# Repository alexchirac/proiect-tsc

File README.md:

## © Copyright Chirac Alexandru-Stefan 333CA

# Hardware Overview and Component Specifications

This document outlines the key hardware components used in the system, including their roles and detailed specifications.

---

## 📑 Table of Contents

- [Main Controller](#main-controller)
- [Display System](#display-system)
- [Power](#power)
- [Memory and Storage](#memory-and-storage)
- [Sensors](#sensors)
- [Connectivity](#connectivity)
- [Block diagram](#block-diagram)
- [Pin Assignments](#pin-assignments)
- [Bill of Materials](#bill-of-materials)

---

## Main Controller

### ESP32-C6-WROOM-1-N8
- **Function**: Core microcontroller that manages all system operations.

---

## Display System

### E-Paper Display
- **Drive Circuit**: Custom electronics for controlling the display.
- **Display Type Selector**: Configurable support for different e-paper types.

---

## Power

### LDO Voltage Regulator — XC6220A331MR-G
- **Function**: Supplies regulated 3.3V to the system.
- **Input Voltage**: Up to 6.0 V
- **Output Current**: Up to 700 mA

### Battery Charger — MCP73831
- **Function**: Manages Li-Po battery charging.
- **Charge Current**: Up to 500 mA (programmable)
- **Charge Voltage**: Fixed at 4.2 V
- **Input Voltage**: Typically 5 V (USB)
- **Features**: Thermal protection, automatic termination, LED status indicator

### Battery Fuel Gauge — MAX17048G+T10
- **Function**: Monitors battery state-of-charge and voltage.
- **Interface**: I2C
- **Voltage Accuracy**: ±7.5 mV
- **Current Consumption**: ~23 µA

### Supercapacitor — CPH3225A
- **Function**: Provides short-term backup power during power loss.

### Diode — MBR0530
- **Function**: Reverse voltage protection and efficient switching.
- **Max Current**: 0.5 A
- **Forward Voltage**: ~0.3–0.4 V

---

## Memory and Storage

### External NOR Flash — W25Q512JVEIQ
- **Function**: High-capacity external storage.
- **Capacity**: 512 Mbit (64 MB)
- **Interface**: SPI
- **Voltage**: 3.3 V
- **Usage**: Firmware, configuration data, graphical assets

### SD Card Slot
- **Function**: Expandable storage option for user or application data.

---

## Sensors

### Environmental Sensor — BME688
- **Function**: Measures environmental data.
- **Measurements**: Temperature, Humidity, Pressure, VOC gas
- **Interface**: I2C
- **Operating Voltage**: 1.7 V – 3.6 V

### RTC Module — DS3231SN
- **Function**: Maintains accurate timekeeping.
- **Accuracy**: ±2 ppm (~1 minute/year)
- **Interface**: I2C
- **Voltage**: 2.3 V – 5.5 V
- **Feature**: Integrated battery backup

---

## Connectivity

### USB-C Connector
- **Function**: Provides both power input and data communication.

### ESD Protection — USBLC6-2SC6Y
- **Function**: Protects USB lines from electrostatic discharge.

### Qwiic/Stemma QT Connector
- **Function**: Supports I2C-based expansion modules.

---

## Block Diagram

---

## Pin Assignments

| ESP32-C6 Pin | Function       | Connected To               | Description                           |
|--------------|----------------|----------------------------|---------------------------------------|
| 3            | RESET          | Reset Button               | System hardware reset                 |
| 4            | SS_SD          | SD Card (pin 2)            | SPI Slave Select for SD card          |
| 6            | SCK            | SD Card (pin 5)            | SPI Clock signal                      |
| 7            | MOSI           | SD Card (pin 3)            | SPI Master Out Slave In               |
| 8            | INT_RTC        | RTC Module (pin 3)         | Interrupt signal from RTC             |
| 9            | 32KHz          | RTC Module (pin 1)         | 32KHz clock signal from RTC           |
| 13           | USB_D-         | USB-C Connector (pin 3)    | USB Data Negative line                |
| 14           | USB_D+         | USB-C Connector (pin 1)    | USB Data Positive line                |
| 15           | IO/BOOT        | Boot Button                | Boot mode selector button             |
| 16           | RTC_RST        | RTC Module (pin 4)         | RTC reset control                     |
| 17           | I2C_PW         | BME688 Sensor (pins 6, 8, 2)| Power control for environmental sensor|
| 19           | SDA            | Multiple I²C devices       | I²C Serial Data line (shared)         |
| 20           | SCL            | Multiple I²C devices       | I²C Serial Clock line (shared)        |
| 23           | IO/CHANGE      | Change Button              | Display/Mode change button            |
| 27           | MISO           | SD Card (pin 7)            | SPI Master In Slave Out               |

---

## Bill of Materials

 | Device | Qty | PURCHASE-URL |
 |--------|-----|--------------|
 | ADAFRUIT_LEDCHIP-LED0603 | 1 | https://www.snapeda.com/parts/KP-1608SURCK/Kingbright/view-part/?ref=search&t=LED%200603 | 
 | EAGLE-LTSPICE_CC0402 | 1 | https://componentsearchengine.com/part-view/CC0402MRX5R5BB106/YAGEO | 
 | RCL_CPOL-EUCT3528 | 1 | https://a360.co/4iZy6AA | 
 | SJ | 1 | https://grabcad.com/library/solder-jumpers-1 | 
 | VARISTOR_3216 | 1 | https://www.mouser.co.uk/ProductDetail/EPCOS-TDK/B72520T0350K062?qs=dEfas%2FXlABIszF52uu7vrg%3D%3D | 
 | EAGLE-LTSPICE_CC0402 | 1 | https://componentsearchengine.com/part-view/CC0402MRX5R5BB106/YAGEO | 
 | ESP32_WROVER_EAGLE-LTSPICE_RR0402 | 1 | https://componentsearchengine.com/part-view/R0402%201%25%20100%20K%20(RC0402FR-07100KL)/YAGEO | 
 | EAGLE-LTSPICE_CC0402 | 1 | https://componentsearchengine.com/part-view/CC0402MRX5R5BB106/YAGEO | 
 | ESP32_WROVER_EAGLE-LTSPICE_RR0402 | 1 | https://componentsearchengine.com/part-view/R0402%201%25%20100%20K%20(RC0402FR-07100KL)/YAGEO | 
 | EAGLE-LTSPICE_CC0402 | 7 | https://componentsearchengine.com/part-view/CC0402MRX5R5BB106/YAGEO | 
 | ESP32_WROVER_EAGLE-LTSPICE_RR0402 | 16 | https://componentsearchengine.com/part-view/R0402%201%%20100%20K%20(RC0402FR-07100KL)/YAGEO | 
 | EAGLE-LTSPICE_CC0402 | 1 | https://componentsearchengine.com/part-view/CC0402MRX5R5BB106/YAGEO | 
 | 112A-TAAR-R03_ATTEND | 1 | https://store.comet.srl.ro/Catalogue/Product/43497/ | 
 | ESP32_WROVER_EAGLE-LTSPICE_RR0402 | 1 | https://componentsearchengine.com/part-view/R0402%201%25%20100%20K%20(RC0402FR-07100KL)/YAGEO | 
 | EAGLE-LTSPICE_CC0402 | 1 | https://componentsearchengine.com/part-view/CC0402MRX5R5BB106/YAGEO | 
 | EAGLE-LTSPICE_CC0402 | 8 | https://componentsearchengine.com/part-view/CC0402MRX5R5BB106/YAGEO | 
 | EAGLE-LTSPICE_CC0402 | 1 | https://componentsearchengine.com/part-view/CC0402MRX5R5BB106/YAGEO | 
 | ESP32_WROVER_EAGLE-LTSPICE_RR0402 | 1 | https://componentsearchengine.com/part-view/R0402%201%25%20100%20K%20(RC0402FR-07100KL)/YAGEO | 
 | ESP32_WROVER_EAGLE-LTSPICE_RR0402 | 1 | https://componentsearchengine.com/part-view/R0402%201%25%20100%20K%20(RC0402FR-07100KL)/YAGEO | 
 | ESP32_WROVER_SPARKFUN-DISCRETESEMI_MOSFET_PCH-DMG2305UX-7 | 2 | https://componentsearchengine.com/part-view/SI1308EDL-T1-GE3/Vishay | 
 | ESP32_WROVER_EAGLE-LTSPICE_RR0402 | 1 | https://componentsearchengine.com/part-view/R0402%201%25%20100%20K%20(RC0402FR-07100KL)/YAGEO | 
 | EAGLE-LTSPICE_CC0402 | 1 | https://componentsearchengine.com/part-view/CC0402MRX5R5BB106/YAGEO | 
 | EAGLE-LTSPICE_CC0402 | 3 | https://componentsearchengine.com/part-view/CC0402MRX5R5BB106/YAGEO | 
 | EAGLE-LTSPICE_CC0402 | 1 | https://componentsearchengine.com/part-view/CC0402MRX5R5BB106/YAGEO | 
 | ESP32_WROVER_EAGLE-LTSPICE_RR0402 | 2 | https://componentsearchengine.com/part-view/R0402%201%25%20100%20K%20(RC0402FR-07100KL)/YAGEO | 
 | 744043680IND_4828-WE-TPC_WRE | 1 | https://eu.mouser.com/ProductDetail/Wurth-Elektronik/744043680?qs=PGXP4M47uW6VkZq%252BkzjrHA%3D%3D | 
 | BD5229G-TR | 1 | https://componentsearchengine.com/part-view/BD5229G-TR/ROHM%20Semiconductor | 
 | BUTTON_CUSYOMV1PACKAGE | 3 | https://www.snapeda.com/parts/EVQP7L01P/Panasonic/view-part/?ref=search&t=evqp7l | 
 | CPH3225A | 1 | https://www.snapeda.com/api/url_track_click_mouser/?unipart_id=562593&manufacturer=Seiko%20Instruments&part_name=CPH3225A&search_term=None | 
 | DS3231SN# | 1 | https://www.snapeda.com/api/url_track_click_mouser/?unipart_id=99048&manufacturer=Analog%20Devices&part_name=DS3231SN#&search_term=None | 
 | ESP32-C6-WROOM-1-N8 | 1 | https://www.snapeda.com/parts/ESP32-C6-WROOM-1-N8/Espressif+Systems/view-part/?ref=eda | 
 | ESP32_WROVER_AVX---SD0805S020S1R0_AVX_ SD0805S020S1R0_0_0AVX_SD0805S020S1R0_0_0 | 2 | https://eu.mouser.com/ProductDetail/KYOCERA-AVX/SD0805S020S1R0?qs=jCA%252BPfw4LHbpkAoSnwrdjw%3D%3D | 
 | ESP32_WROVER_BME680_BME680 | 1 | https://www.snapeda.com/parts/BME680/Bosch/view-part/?welcome=home | 
 | ESP32_WROVER_SPARKFUN-IC-POWER_MCP73831 | 1 | https://www.digikey.ro/en/products/detail/microchip-technology/MCP73831T-2ACI-OT/964301 | 
 | FH34SRJ-24S-0.5SH_99_ | 1 | https://componentsearchengine.com/part-view/XC6220A331MR-G/Torex | 
 | MAX17048G+T10 | 1 | https://www.snapeda.com/api/url_track_click_mouser/?unipart_id=329239&manufacturer=Analog%20Devices&part_name=MAX17048G+T10&search_term=None | 
 | MBR0530 | 3 | https://www.snapeda.com/api/url_track_click_mouser/?unipart_id=179458&manufacturer=ON%20Semiconductor&part_name=MBR0530&search_term=None | 
 | PGB1010603MR | 6 | https://www.snapeda.com/api/url_track_click_mouser/?unipart_id=5659453&manufacturer=Littelfuse%20Inc.&part_name=PGB1010603MR&search_term=None | 
 | QWIIC_CONNECTORJS-1MM | 1 | https://www.digikey.ro/en/models/926710 | 
 | SAMACSYS_PARTS_USB4110-GF-A | 1 | https://componentsearchengine.com/part-view/USB4110-GF-A/GCT%20(GLOBAL%20CONNECTOR%20TECHNOLOGY) | 
 | SI1308EDL-T1-GE3 | 1 | https://componentsearchengine.com/part-view/SI1308EDL-T1-GE3/Vishay | 
 | TPTP20R | 17 | https://grabcad.com/library/test-points-printed-circuit-board-1 | 
 | USBLC6-2SC6Y | 1 | https://www.snapeda.com/parts/USBLC6-2SC6Y/STMicroelectronics/view-part/?ref=eda | 
 | W25Q512JVEIQ | 1 | https://www.snapeda.com/parts/W25Q512JVEIQ/Winbond+Electronics/view-part/?ref=eda |

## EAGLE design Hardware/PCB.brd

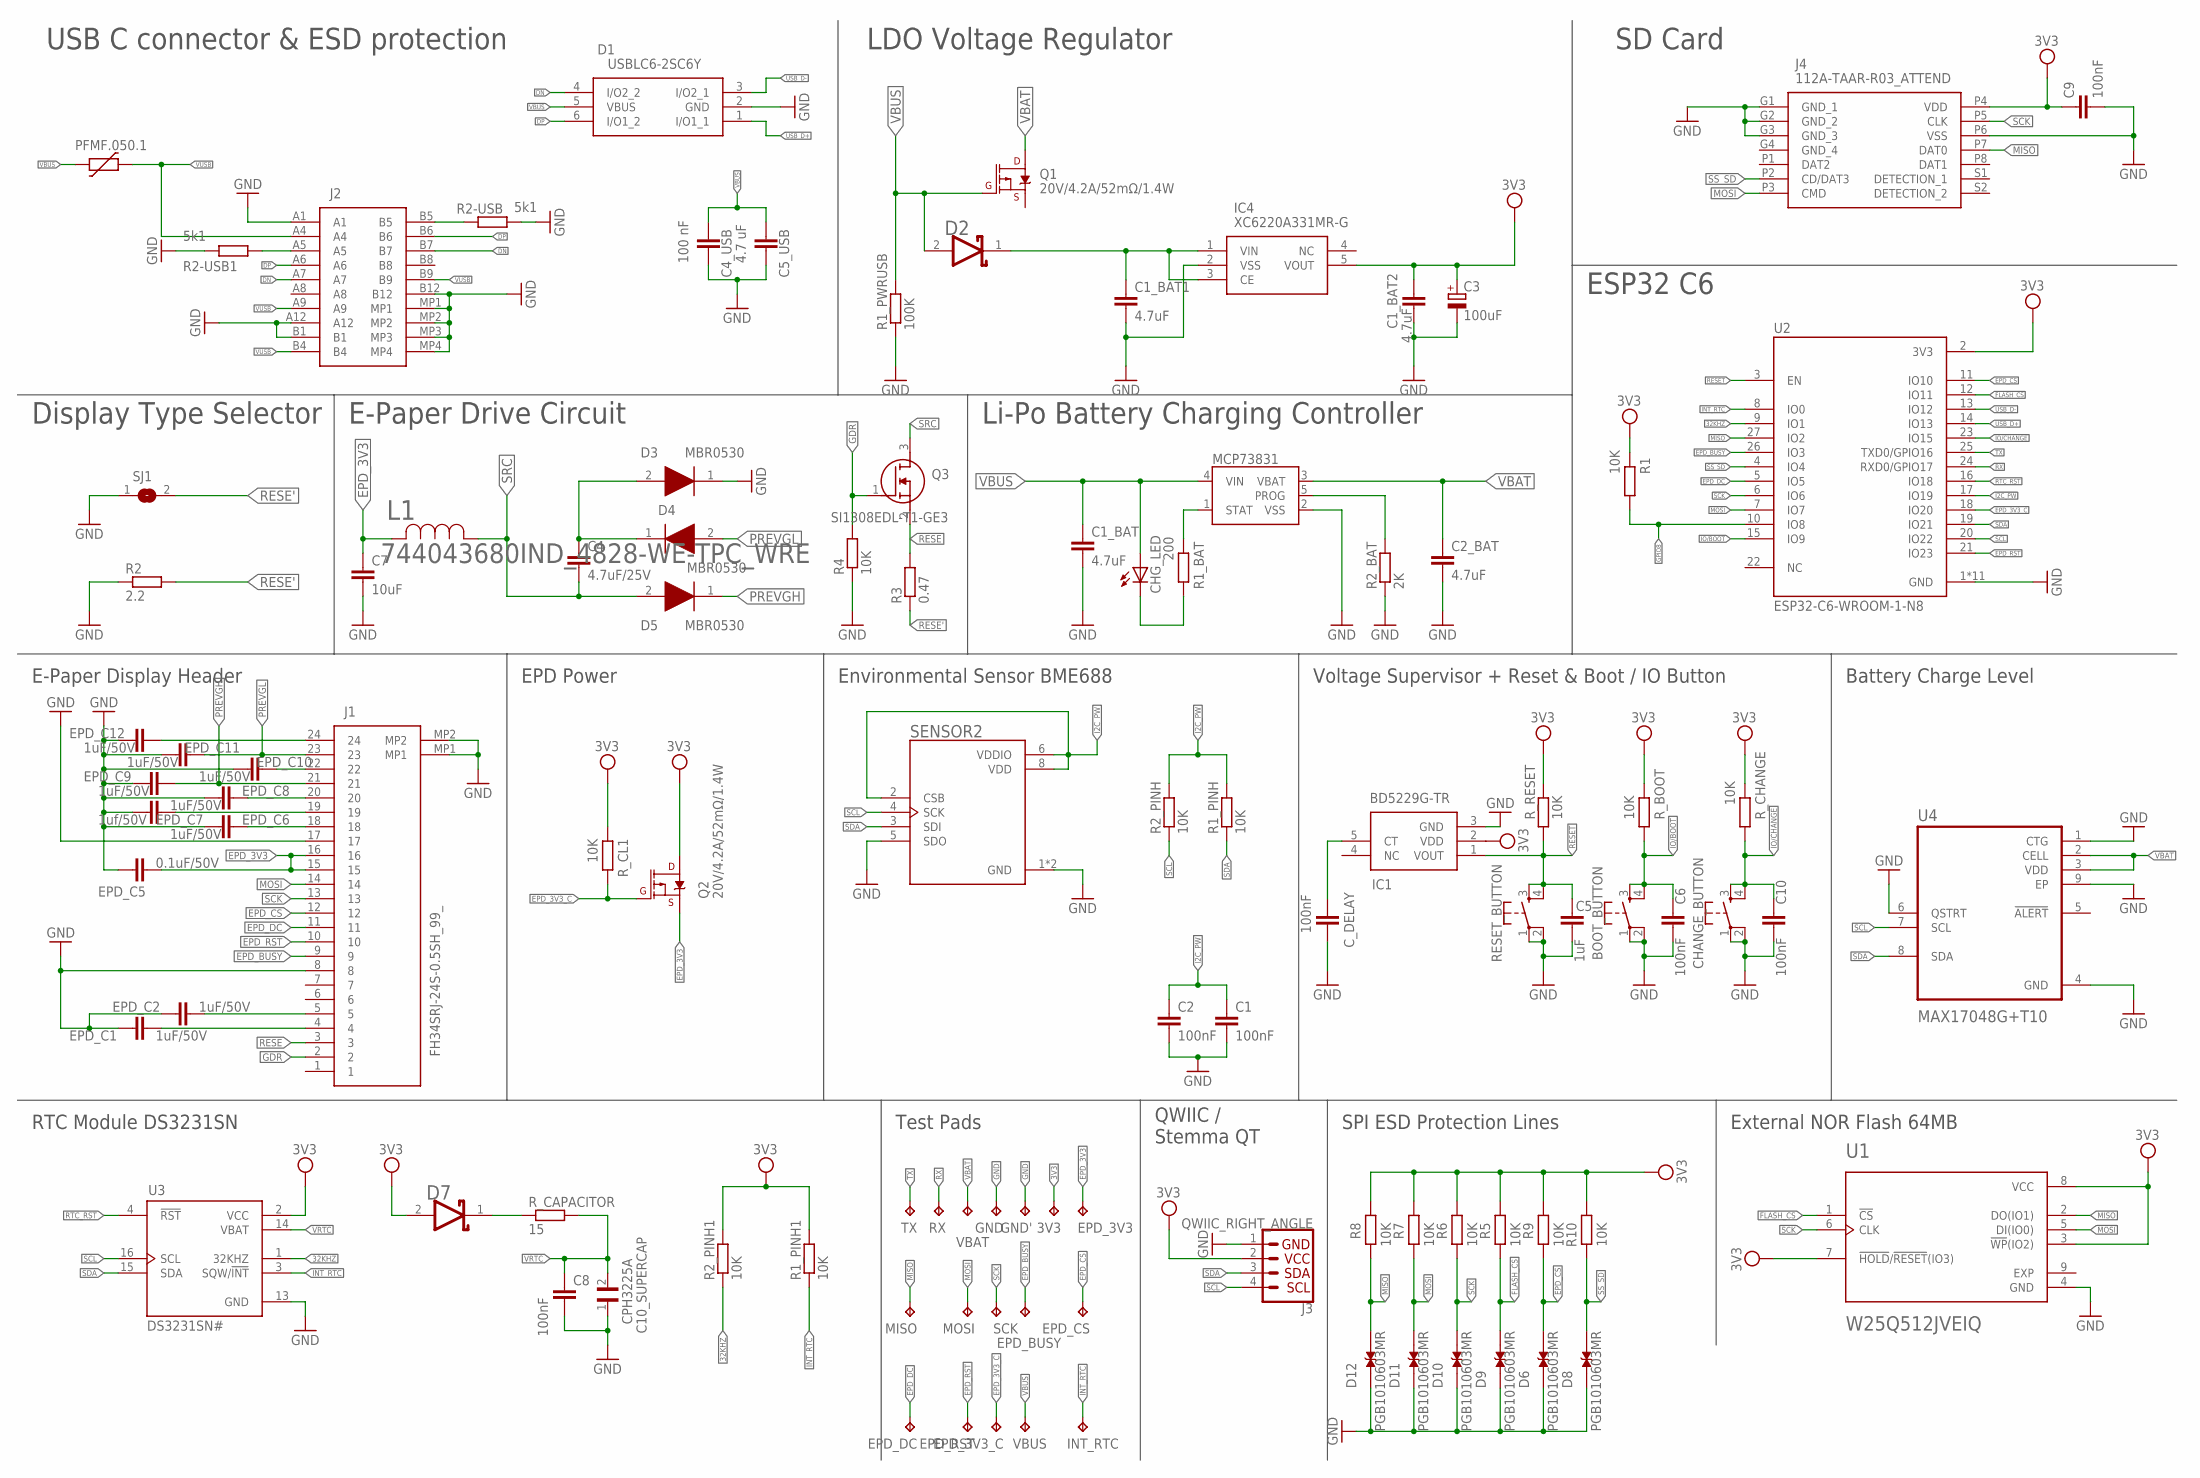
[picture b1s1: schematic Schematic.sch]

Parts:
3V3: TPTP20R; TP20R
BOOT_BUTTON: BUTTON_CUSYOMV1PACKAGE; MYBUTTON
C1, C2, C6, C8, C9, C10: 100nF; EAGLE-LTSPICE_C0402
C1_BAT, C1_BAT1, C1_BAT2, C2_BAT: 4.7uF; EAGLE-LTSPICE_C0402
C3: 100uF; RCL_CT3528
C4: 4.7uF/25V; EAGLE-LTSPICE_C0402
C4_USB: 100 nF; EAGLE-LTSPICE_C0402
C5: 1uF; EAGLE-LTSPICE_C0402
C5_USB: 4.7 uF; EAGLE-LTSPICE_C0402
C7: 10uF; EAGLE-LTSPICE_C0402
C10_SUPERCAP: CPH3225A; CAPCP3225X100N
CHANGE_BUTTON: BUTTON_CUSYOMV1PACKAGE; MYBUTTON
CHG_LED: ADAFRUIT_LEDCHIP-LED0603; ADAFRUIT_CHIP-LED0603
C_DELAY: 100nF; EAGLE-LTSPICE_C0402
D1: USBLC6-2SC6Y; SOT95P280X145-6N
D2, D7: ESP32_WROVER_AVX---SD0805S020S1R0_AVX_SD0805S020S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; ESP32_WROVER_AVX---SD0805S020S1R0_AVX_SD0805S020S1R0_0
D3, D4, D5: MBR0530; SOD3716X135N
D6, D8, D9, D10, D11, D12: PGB1010603MR; DIOC1608X36N
EPD_3V3, EPD_3V3_C: TPTP20R; TP20R
EPD_BUSY: TPTP20R; TP20R
EPD_C1, EPD_C2, EPD_C6, EPD_C8, EPD_C9, EPD_C10, EPD_C11, EPD_C12: 1uF/50V; EAGLE-LTSPICE_C0402
EPD_C5: 0.1uF/50V; EAGLE-LTSPICE_C0402
EPD_C7: 1uf/50V; EAGLE-LTSPICE_C0402
EPD_CS: TPTP20R; TP20R
EPD_DC: TPTP20R; TP20R
EPD_RST: TPTP20R; TP20R
GND: TPTP20R; TP20R
GND': TPTP20R; TP20R
IC1: BD5229G-TR; SOT95P280X125-5N
IC4: XC6220A331MR-G; SOT95P280X120-5N
INT_RTC: TPTP20R; TP20R
J1: FH34SRJ-24S-0.5SH_99_; FH34SRJ24S05SH99
J2: SAMACSYS_PARTS_USB4110-GF-A; SAMACSYS_PARTS_USB4110GFA
J3: QWIIC_RIGHT_ANGLE; JST04_1MM_RA
J4: 112A-TAAR-R03_ATTEND; 112ATAARR03ATTEND
L1: 744043680IND_4828-WE-TPC_WRE; IND_4828-WE-TPC_WRE
MCP73831: ESP32_WROVER_SPARKFUN-IC-POWER_MCP73831; ESP32_WROVER_SPARKFUN-IC-POWER_SOT23-5
MISO: TPTP20R; TP20R
MOSI: TPTP20R; TP20R
PFMF.050.1: VARISTOR_3216; VARC3216X102N
Q1, Q2: 20V/4.2A/52mΩ/1.4W; ESP32_WROVER_SPARKFUN-DISCRETESEMI_SOT23-3
Q3: SI1308EDL-T1-GE3; SOT65P210X110-3N
R1, R1_PINH, R1_PINH1, R2_PINH, R2_PINH1, R4, R5, R6, R7, R8, R9, R10: 10K; ESP32_WROVER_EAGLE-LTSPICE_R0402
R1_BAT: 200; ESP32_WROVER_EAGLE-LTSPICE_R0402
R1_PWRUSB: 100K; ESP32_WROVER_EAGLE-LTSPICE_R0402
R2: 2.2; ESP32_WROVER_EAGLE-LTSPICE_R0402
R2-USB, R2-USB1: 5k1; ESP32_WROVER_EAGLE-LTSPICE_R0402
R2_BAT: 2K; ESP32_WROVER_EAGLE-LTSPICE_R0402
R3: 0.47; ESP32_WROVER_EAGLE-LTSPICE_R0402
RESET_BUTTON: BUTTON_CUSYOMV1PACKAGE; MYBUTTON
RX: TPTP20R; TP20R
R_BOOT: 10K; ESP32_WROVER_EAGLE-LTSPICE_R0402
R_CAPACITOR: 15; ESP32_WROVER_EAGLE-LTSPICE_R0402
R_CHANGE: 10K; ESP32_WROVER_EAGLE-LTSPICE_R0402
R_CL1: 10K; ESP32_WROVER_EAGLE-LTSPICE_R0402
R_RESET: 10K; ESP32_WROVER_EAGLE-LTSPICE_R0402
SCK: TPTP20R; TP20R
SENSOR2: ESP32_WROVER_BME680_BME680; ESP32_WROVER_BME680_PSON80P300X300X100-8N
SJ1: SJ
TX: TPTP20R; TP20R
U1: W25Q512JVEIQ; SON127P600X800X80-9N
U2: ESP32-C6-WROOM-1-N8; XCVR_ESP32-C6-WROOM-1-N8
U3: DS3231SN#; SOIC127P1032X265-16N
U4: MAX17048G+T10; SON50P200X200X80-9N
VBAT: TPTP20R; TP20R
VBUS: TPTP20R; TP20R

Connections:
3V3: 3V3.TP, C1_BAT2.1, C3.+, C9.1, D7.2 (ANODE), IC1.2 (VDD), IC4.5 (VOUT), J3.2, J4.P4 (VDD), Q2.3 (D), R1.2, R1_PINH1.2, R2_PINH1.2, R5.1, R6.1, R7.1, R8.1, R9.1, R10.1, R_BOOT.2, R_CHANGE.2, R_CL1.2, R_RESET.2, U1.3 (!WP!(IO2)), U1.7 (!HOLD!/!RESET!(IO3)), U1.8 (VCC), U2.2 (3V3), U3.2 (VCC)
32KHZ: R2_PINH1.1, U2.9 (IO1), U3.1 (32KHZ)
DN: D1.4 (I/O2_2), J2.A7, J2.B7
DP: D1.6 (I/O1_2), J2.A6, J2.B6
EPD_3V3: C7.1, EPD_3V3.TP, EPD_C5.1, J1.15, J1.16, L1.2, Q2.2 (S)
EPD_3V3_C: EPD_3V3_C.TP, Q2.1 (G), R_CL1.1, U2.18 (IO20)
EPD_BUSY: EPD_BUSY.TP, J1.9, U2.26 (IO3)
EPD_CS: D6.2, EPD_CS.TP, J1.12, R9.2, U2.11 (IO10)
EPD_DC: EPD_DC.TP, J1.11, U2.5 (IO5)
EPD_RST: EPD_RST.TP, J1.10, U2.21 (IO23)
FLASH_CS: D9.2, R5.2, U1.1 (!CS), U2.12 (IO11)
GDR: J1.2, Q3.1 (G), R4.2
GND: BOOT_BUTTON.1, BOOT_BUTTON.2, C1.2, C1_BAT.2, C1_BAT1.2, C1_BAT2.2, C2.2, C2_BAT.2, C3.-, C4_USB.2, C5.2, C5_USB.2, C6.2, C7.2, C8.2, C9.2, C10.2, C10_SUPERCAP.1, CHANGE_BUTTON.1, CHANGE_BUTTON.2, C_DELAY.2, D1.2 (GND), D3.1 (K), D6.1, D8.1, D9.1, D10.1, D11.1, D12.1, EPD_C1.2, EPD_C2.2, EPD_C5.2, EPD_C6.2, EPD_C7.2, EPD_C8.2, EPD_C9.2, EPD_C10.2, EPD_C11.2, EPD_C12.2, GND.TP, GND'.TP, IC1.3 (GND), IC4.2 (VSS), J1.8, J1.17, J1.MP1, J1.MP2, J2.A1, J2.A12, J2.B1, J2.B12, J2.MP1, J2.MP2, J2.MP3, J2.MP4, J3.1, J4.G1 (GND_1), J4.G2 (GND_2), J4.G3 (GND_3), J4.P6 (VSS), MCP73831.2 (VSS), R1_PWRUSB.1, R2.1, R2-USB.2, R2-USB1.1, R2_BAT.1, R4.1, RESET_BUTTON.1, RESET_BUTTON.2, SENSOR2.1 (GND), SENSOR2.5 (SDO), SENSOR2.7 (GND), SJ1.1, U1.4 (GND), U2.1 (GND), U2.28 (GND), U2.29_1 (GND), U2.29_2 (GND), U2.29_3 (GND), U2.29_4 (GND), U2.29_5 (GND), U2.29_6 (GND), U2.29_7 (GND), U2.29_8 (GND), U2.29_9 (GND), U3.13 (GND), U4.1 (CTG), U4.4 (GND), U4.6 (QSTRT), U4.9 (EP)
GPIO8: R1.1, U2.10 (IO8)
I2C_PW: C1.1, C2.1, R1_PINH.2, R2_PINH.2, SENSOR2.2 (CSB), SENSOR2.6 (VDDIO), SENSOR2.8 (VDD), U2.17 (IO19)
INT_RTC: INT_RTC.TP, R1_PINH1.1, U2.8 (IO0), U3.3 (SQW/!INT)
IO/BOOT: BOOT_BUTTON.3, BOOT_BUTTON.4, C6.1, R_BOOT.1, U2.15 (IO9)
IO/CHANGE: C10.1, CHANGE_BUTTON.3, CHANGE_BUTTON.4, R_CHANGE.1, U2.23 (IO15)
MISO: D12.2, J4.P7 (DAT0), MISO.TP, R8.2, U1.2 (DO(IO1)), U2.27 (IO2)
MOSI: D11.2, J1.14, J4.P3 (CMD), MOSI.TP, R7.2, U1.5 (DI(IO0)), U2.7 (IO7)
unnamed: J2.A5, R2-USB1.2
unnamed: J2.B5, R2-USB.1
unnamed: MCP73831.5 (PROG), R2_BAT.2
unnamed: C1_BAT1.1, D2.1 (CATHODE), IC4.1 (VIN), IC4.3 (CE)
unnamed: EPD_C12.1, J1.24
unnamed: EPD_C6.1, J1.18
unnamed: MCP73831.1 (STAT), R1_BAT.2
unnamed: CHG_LED.C, R1_BAT.1
unnamed: C4.1, D3.2 (A), D4.1 (K)
unnamed: EPD_C7.1, J1.19
unnamed: EPD_C8.1, J1.20
unnamed: D7.1 (CATHODE), R_CAPACITOR.1
unnamed: EPD_C10.1, J1.22
unnamed: C_DELAY.1, IC1.5 (CT)
unnamed: EPD_C1.1, J1.4
unnamed: EPD_C2.1, J1.5
PREVGH: D5.1 (K), EPD_C9.1, J1.21
PREVGL: D4.2 (A), EPD_C11.1, J1.23
RESE: J1.3, Q3.2 (S), R3.2
RESE': R2.2, R3.1, SJ1.2
RESET: C5.1, IC1.1 (VOUT), RESET_BUTTON.3, RESET_BUTTON.4, R_RESET.1, U2.3 (EN)
RTC_RST: U2.16 (IO18), U3.4 (!RST)
RX: RX.TP, U2.24 (RXD0/GPIO17)
SCK: D10.2, J1.13, J4.P5 (CLK), R6.2, SCK.TP, U1.6 (CLK), U2.6 (IO6)
SCL: J3.4, R2_PINH.1, SENSOR2.4 (SCK), U2.20 (IO22), U3.16 (SCL), U4.7 (SCL)
SDA: J3.3, R1_PINH.1, SENSOR2.3 (SDI), U2.19 (IO21), U3.15 (SDA), U4.8 (SDA)
SRC: C4.2, D5.2 (A), L1.1, Q3.3 (D)
SS_SD: D8.2, J4.P2 (CD/DAT3), R10.2, U2.4 (IO4)
TX: TX.TP, U2.25 (TXD0/GPIO16)
USB_D+: D1.1 (I/O1_1), U2.14 (IO13)
USB_D-: D1.3 (I/O2_1), U2.13 (IO12)
VBAT: C2_BAT.1, MCP73831.3 (VBAT), Q1.3 (D), U4.2 (CELL), U4.3 (VDD), VBAT.TP
VBUS: C1_BAT.1, C4_USB.1, C5_USB.1, CHG_LED.A, D1.5 (VBUS), D2.2 (ANODE), MCP73831.4 (VIN), PFMF.050.1.1, Q1.1 (G), R1_PWRUSB.2, VBUS.TP
VRTC: C8.1, C10_SUPERCAP.2, R_CAPACITOR.2, U3.14 (VBAT)
VUSB: J2.A4, J2.A9, J2.B4, J2.B9, PFMF.050.1.2

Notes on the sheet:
USB C connector & ESD protection
LDO Voltage Regulator
SD Card
ESP32 C6
Display Type Selector
E-Paper Drive Circuit
Li-Po Battery Charging Controller
E-Paper Display Header
EPD Power
Environmental Sensor BME688
Voltage Supervisor + Reset & Boot / IO Button
Battery Charge Level
RTC Module DS3231SN
Test Pads
QWIIC / Stemma QT
SPI ESD Protection Lines
External NOR Flash 64MB

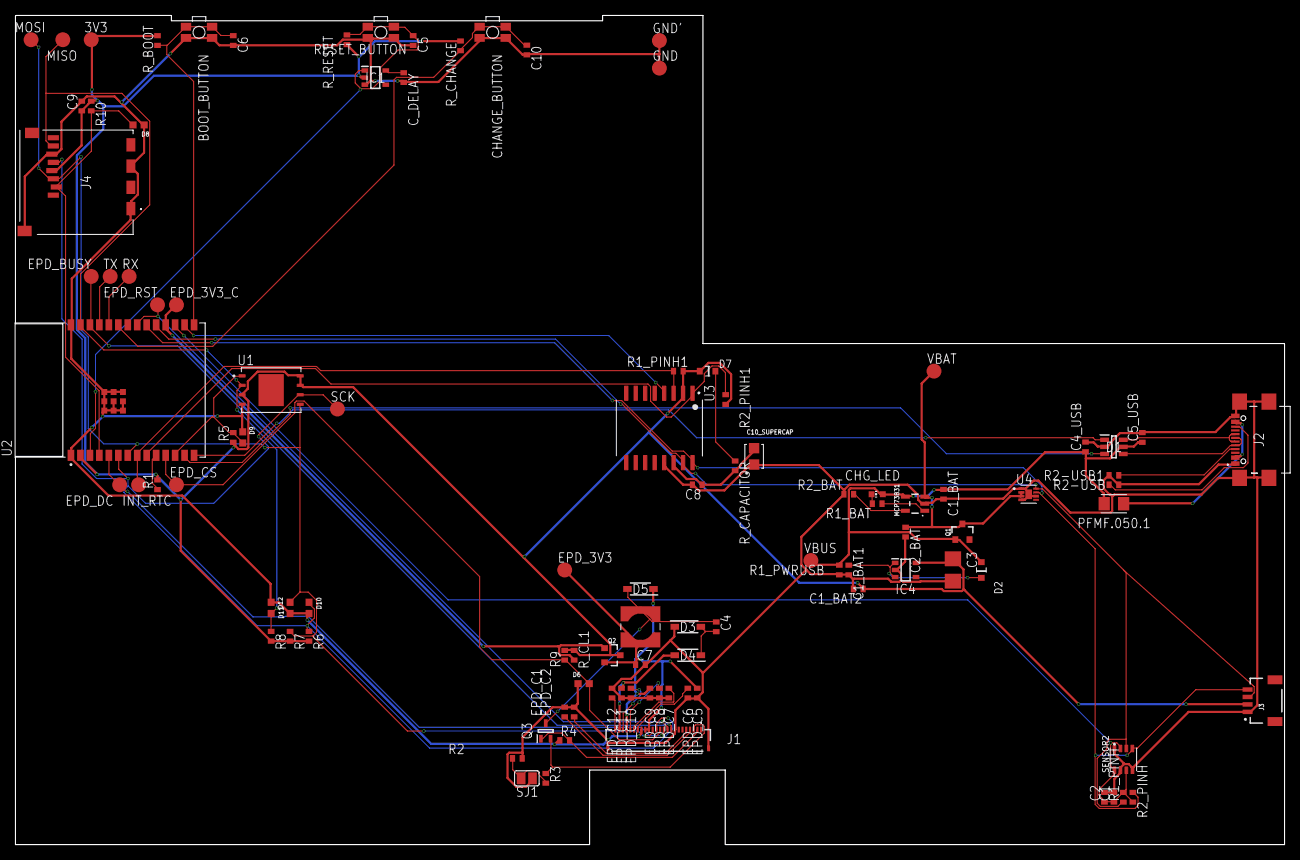
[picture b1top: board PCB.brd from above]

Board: 2 copper layers, 170.2 x 111.2 mm, 103 parts (0 on the bottom side), 55 nets.

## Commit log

2025-04-05 Create LICENSE
2025-04-06 Added Exploded View video
2025-04-06 Done without README
2025-04-06 Started README
2025-04-06 Added descriptions and BOM to README
2025-04-06 Fixed Table Of Contents
2025-04-15 Solved Issues

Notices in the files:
parts and their libraries:
COPYRIGHT: Copyright (C) 2024 Ultra Librarian. All rights reserved.
